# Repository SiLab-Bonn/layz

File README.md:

# layz

Layout tools for SiLab's FR4 PCBs, in-house RDL chips (maskless lithography) and the flex PCBs
that connect them, as one command line tool:

```
layz drc       design rule check of a GDS (gdscheck, with the kit's deck)
layz pcb       GDS -> KiCad .kicad_pcb (copper zones, footprints, vias, outline, stackup)
layz nets      assign zone/via nets from a seed footprint's pad nets
layz hyp       .kicad_pcb or GDS -> HyperLynx .hyp (for SI/PI)
layz svg       GDS -> SVG preview
layz pex       3-D capacitance matrix with FasterCap/FastCap2 (.kicad_pcb, or GDS + stack)
layz field     electric field and potential from a `layz pex --charges` run
layz view      open a result: DRC report in KLayout, or ParaView renders of a field run
layz doctor    which external tools this machine has
```

`layz <command> -h` shows each command's options.

## Install

layz is a standard Python package (`pyproject.toml`, Python 3.12 to 3.15), installed with
Python's own `venv` and `pip`. It also uses tools that are not on PyPI:

| Tool | Needed for | Linux | macOS |
| --- | --- | --- | --- |
| KiCad (its `pcbnew` Python module, `kicad-cli`) | `pcb`, `hyp`, `pex` on boards, schematic netlists | [kicad.org/download/linux](https://www.kicad.org/download/linux/) | [kicad.org/download/macos](https://www.kicad.org/download/macos/) |
| KLayout | viewing GDS and DRC results | [klayout.de/build.html](https://www.klayout.de/build.html) | [klayout.de/build.html](https://www.klayout.de/build.html) |
| FasterCap (default) / FastCap2 | `pex`, `field` | `scripts/build_solvers.sh` (sources: [FasterCap](https://github.com/iic-jku/FasterCap), [FastCap2](https://github.com/martinjankoehler/FastCap2)) | [FasterCap releases](https://github.com/iic-jku/FasterCap/releases) (or `scripts/build_solvers.sh`) |
| gdscheck | `drc` | [github.com/aesc-silicon/gdscheck](https://github.com/aesc-silicon/gdscheck), with Rust's `cargo` ([rust-lang.org/tools/install](https://www.rust-lang.org/tools/install)) | same |
| ParaView (optional) | `view` of field results | [paraview.org/download](https://www.paraview.org/download/) | [paraview.org/download](https://www.paraview.org/download/) |

gdscheck installs with `cargo install --git https://github.com/aesc-silicon/gdscheck gdscheck`.

KLayout's Python module, KLayout-PEX, Shapely and the rest come from PyPI. From the repo root:

```sh
./install.sh                # once; again after a pull that changes dependencies
layz doctor                 # checks klayout, kicad-cli, FasterCap and gdscheck, and more
```

`install.sh` (bash; works from zsh too, on Linux and macOS) makes `.venv/` with the Python that
KiCad's `pcbnew` module is built for (Linux: `python3`, 3.14 on Ubuntu 26.04; macOS: KiCad's own),
checks it's Python 3.12 to 3.15, installs layz into it with `pip install --editable .` (changes in
this repo take effect directly), links `layz` into `~/.local/bin`, and adds that folder to `PATH`
in `~/.bashrc` or `~/.zshrc` if it isn't there yet. `./install.sh --test` also installs pytest,
`./install.sh --uninstall` removes the link. Keep the clone: the DRC decks (`drc/`) and stacks
(`stacks/`) are read from it.

By hand, the same is:

```sh
python3 -m venv --system-site-packages .venv      # system packages: pcbnew comes with KiCad
.venv/bin/pip install --editable .
ln -sf "$PWD/.venv/bin/layz" ~/.local/bin/layz
```

layz finds KiCad's `pcbnew` by itself, also from a venv without the system's packages; set
`LAYZ_KICAD_PYTHONPATH` to the folder holding `pcbnew.py` if it's somewhere unusual.
`layz doctor` exits with an error when a required tool is missing, and warns about optional
ones (HyperLynx via `LAYZ_HYPERLYNX`, FastCap2, ParaView).

On Ubuntu also `sudo apt install cmake g++ libomp-dev libopenblas-dev`, then
`scripts/build_solvers.sh`: it builds FasterCap (iic-jku fork, headless), FastCap2 and a
wxWidgets base library into `~/.local/share/layz` and links the solvers into `~/.local/bin`.
layz finds them on `PATH`, or through `LAYZ_FASTERCAP` / `LAYZ_FASTCAP2`. On macOS see the notes
at the top of the script.

Tests run in the same venv:

```sh
./install.sh --test
.venv/bin/python -m pytest
```

## Stack files

A GDS carries only 2-D shapes; heights, thicknesses and permittivities come from a **stack
file**, one per process, in `stacks/`. It lists the layers top to bottom; z positions are derived
from the order. Every tool reads the same file:

```toml
name = "SiLab RDL, 4 copper"
outline = "70/0"              # GDS layer of the board/die outline

[[layer]]
name = "F.Mask"
type = "mask"                 # mask | copper | dielectric
thickness_um = 1.0
er = 3.3

[[layer]]
name = "F.Cu"                 # KiCad names: F.Cu, In1.Cu, ..., B.Cu
type = "copper"
thickness_um = 0.5
gds = "8/0"
pads = true                   # GDS sub-cells with these shapes become footprint pads
zones = false                 # top-level shapes become copper zones (default true)

[[layer]]
name = "DE_F.Cu"
type = "dielectric"
thickness_um = 4.0
er = 4.5
material = "FR4"
# ... more layers ...

[[via]]
gds = "7/0"
top = "F.Cu"
bottom = "In1.Cu"
```

`layz pcb --stack` writes the stack into the board as its KiCad physical stackup, so the
`.kicad_pcb`, the `.hyp` and the FasterCap model all carry it. A board made in KiCad uses its
own stackup (Board Setup > Physical Stackup). The full format is documented in
[src/layz/stack.py](src/layz/stack.py).

| Stack file | Process | Source |
| --- | --- | --- |
| `uni_bonn_rdl.toml` | Uni Bonn RDL, Al on polyimide (obelix1: M2 + M3 on the chip pads) | asiclab `tech/uni-bonn-rdl` thicknesses, obelix1 KiCad mapping; polyimide εr and 8/0 to confirm |
| `multicb_4L-01.toml` | Multi-CB 4-layer FR4, 1.6 mm | Multi-CB defined buildup 4L-01 (mask assumed: 10 µm, εr 3.3) |
| `multicb_4L-02.toml` | Multi-CB 4-layer FR4, 1.0 mm | Multi-CB defined buildup 4L-02 (mask assumed) |
| `multicb_flex_2F-l.toml` | Multi-CB 2-layer flex, adhesiveless, 161 µm | Multi-CB standard 2F-l |
| `multicb_flex_2F-a.toml` | Multi-CB 2-layer flex, adhesive-bonded, 187 µm | Multi-CB standard 2F-a |

The Multi-CB files are their published standard buildups; for a board ordered with a custom
buildup, copy the closest one and enter the ordered thicknesses and materials.

## GDS -> KiCad -> HyperLynx

```sh
layz hyp example_files/obelix1_ivtx_ladder_v2.gds --stack stacks/uni_bonn_rdl.toml   # one step
```

or step by step, to edit the board in between:

```sh
layz pcb --lay design.gds --stack stacks/uni_bonn_rdl.toml          # -> design.kicad_pcb
# KiCad: Update PCB from Schematic (references and the seed footprint's pad nets)
layz nets design.kicad_pcb --seed-footprint VTX2       # -> design_nets_assigned.kicad_pcb
layz hyp design_nets_assigned.kicad_pcb               # -> design_nets_assigned.hyp
```

`layz pcb`: GDS cells with pad-layer shapes become footprints (one per cell and orientation),
top-level copper becomes filled zones, via layers become blind/buried vias, the outline layer
becomes Edge.Cuts; Y is flipped so the board shows the GDS top view. `nets`: nets propagate from
the seed footprint's pads through touching copper and vias. `hyp`: a re-implementation of KiCad's
HyperLynx exporter (KiCad has it only in the GUI), same records and number format: board
outline, stackup, devices, padstacks, and per net its pins, vias, tracks and zone fills.

## Design rule check

```sh
layz drc --lay design.gds --kit uni-bonn-rdl                  # -> design.lyrdb
layz view design.lyrdb --lay design.gds                     # KLayout with the violation markers
```

Decks are gdscheck PDKs in its own YAML format, one per kit in `drc/<kit>/`.
`drc/uni-bonn-rdl/` is the in-house RDL (maskless lithography), with the layers of asiclab's
`tech/uni-bonn-rdl`: chip pads 68/0, Al M1 1/0, M2 3/0, M3 6/0, polyimide openings V1 2/0,
V2 4/0, pad openings 7/0, outline 70/0.

| Rule | Value |
| --- | --- |
| M1, M2, M3 width, spacing, notch | ≥ 10 µm |
| M1, M2, M3 area (minimum feature 10 × 10 µm) | ≥ 100 µm² |
| V1, V2, pad opening size / spacing (spacing assumed = metal spacing) | ≥ 10 µm |
| V1 by M2, V2 by M2 and M3, pad openings by M3, every side | ≥ 10 µm (pads ≥ 30 × 30 µm) |
| V1 landing on M1 or a chip pad | contained |
| metal density in any 1 × 1 mm window (step 500 µm), inside the outline 70/0 | ≤ 95 % |

Chip pads (68/0) are the chip's and aren't checked. V2 is the 4/0 opening alone (asiclab's
tech has 4/0 AND 5/0; designs draw V2 on 4/0). `--suite geometry` leaves out density. `--benchmark` times each rule on its own (slowest first):
on the obelix1 ladder the M2 and M3 width checks are 98 % of the run. `--tile` is gdscheck's
merge tile; layz uses 20 mm, about 5x faster than 2 mm on the ladder's long planes. The
obelix1 ladder GDS takes about 35 s (18 threads) and reports 261 violations: V2 enclosure
by M2 (52) and M3 (138), density in 19 + 20 windows on M2/M3, 19 notches, 1 width, and 12 at V1
and pad openings.

## Capacitance and fields

```sh
layz pex board.kicad_pcb                              # stack from the board
layz pex chip.gds --stack stacks/uni_bonn_rdl.toml       # stack from the file
layz pex board.kicad_pcb --charges --out run          # also keep charges for fields
layz field run --voltage TOP=1                        # 3-D grid -> run/field.vtk
layz field run --voltage TOP=1 --plane y=5000         # cross-section, PNG + VTK
layz view section run/section_y5000_edge.vtk          # ParaView: heatmap + field lines
layz view geometry run                                # ParaView: the 3-D model
```

A conductor is any copper that touches or is joined by vias (no LVS, no netlist), named by net
(KiCad), by GDS texts or `--name NAME=LAYER@X,Y`. The 3-D model (extrusion, dielectric interfaces,
triangulation into FasterCap's `.lst`/`.geo`) comes from KLayout-PEX's `FasterCapModelBuilder`.
Results: `maxwell_matrix_fF.csv` (Maxwell sign convention: diagonal total, off-diagonal
−mutual) and `spice_caps_fF.csv`.

**Keep `--tolerance` at 1 % or tighter** (the default). With dielectrics FasterCap's first passes
can be far off: plates with εr = 4 gave 2336 fF at 5 % and 3591 fF at 1 %, without an error.
layz warns when FasterCap stops after a single pass.

`--voltage` sets conductor voltages when computing fields; any bias is a superposition of the
solved columns, so it needs no new solve. On Ubuntu ParaView needs `HWLOC_COMPONENTS=-gl`
(`layz view` sets it).

## Checks

`.venv/bin/python -m pytest` (about 3 s):

- GDS -> `.hyp` of the obelix1 RDL design gives the same STACKUP section as the `.hyp` KiCad's GUI
  exported (`example_files/obelix1_ivtx_ladder_with_nets_v3.1.hyp`).
- `tests/plates.gds`, two 1 mm² plates 10 µm apart in vacuum: 918.8 fF (ideal 885 fF + fringe).
- `tests/pcb_plates.kicad_pcb` (two 10 × 10 mm, 35 µm plates on 0.2 mm FR4, from
  `tests/make_pcb_plates.py`) builds the validated 3-D model. Solved at 1 %: 21.54 pF against
  ~21.7 pF from Palmer's edge-corrected formula, 5.16 kV/m in the FR4 at 1 V (ideal 5.0).
- Stack files: heights, validation, KiCad stackup round trip.

## Files

- `src/layz/` the package; `stacks/` process stacks; `example_files/` reference designs
  (GDS, KiCad schematic, a KiCad-exported `.hyp`); `tests/`; `scripts/build_solvers.sh`.

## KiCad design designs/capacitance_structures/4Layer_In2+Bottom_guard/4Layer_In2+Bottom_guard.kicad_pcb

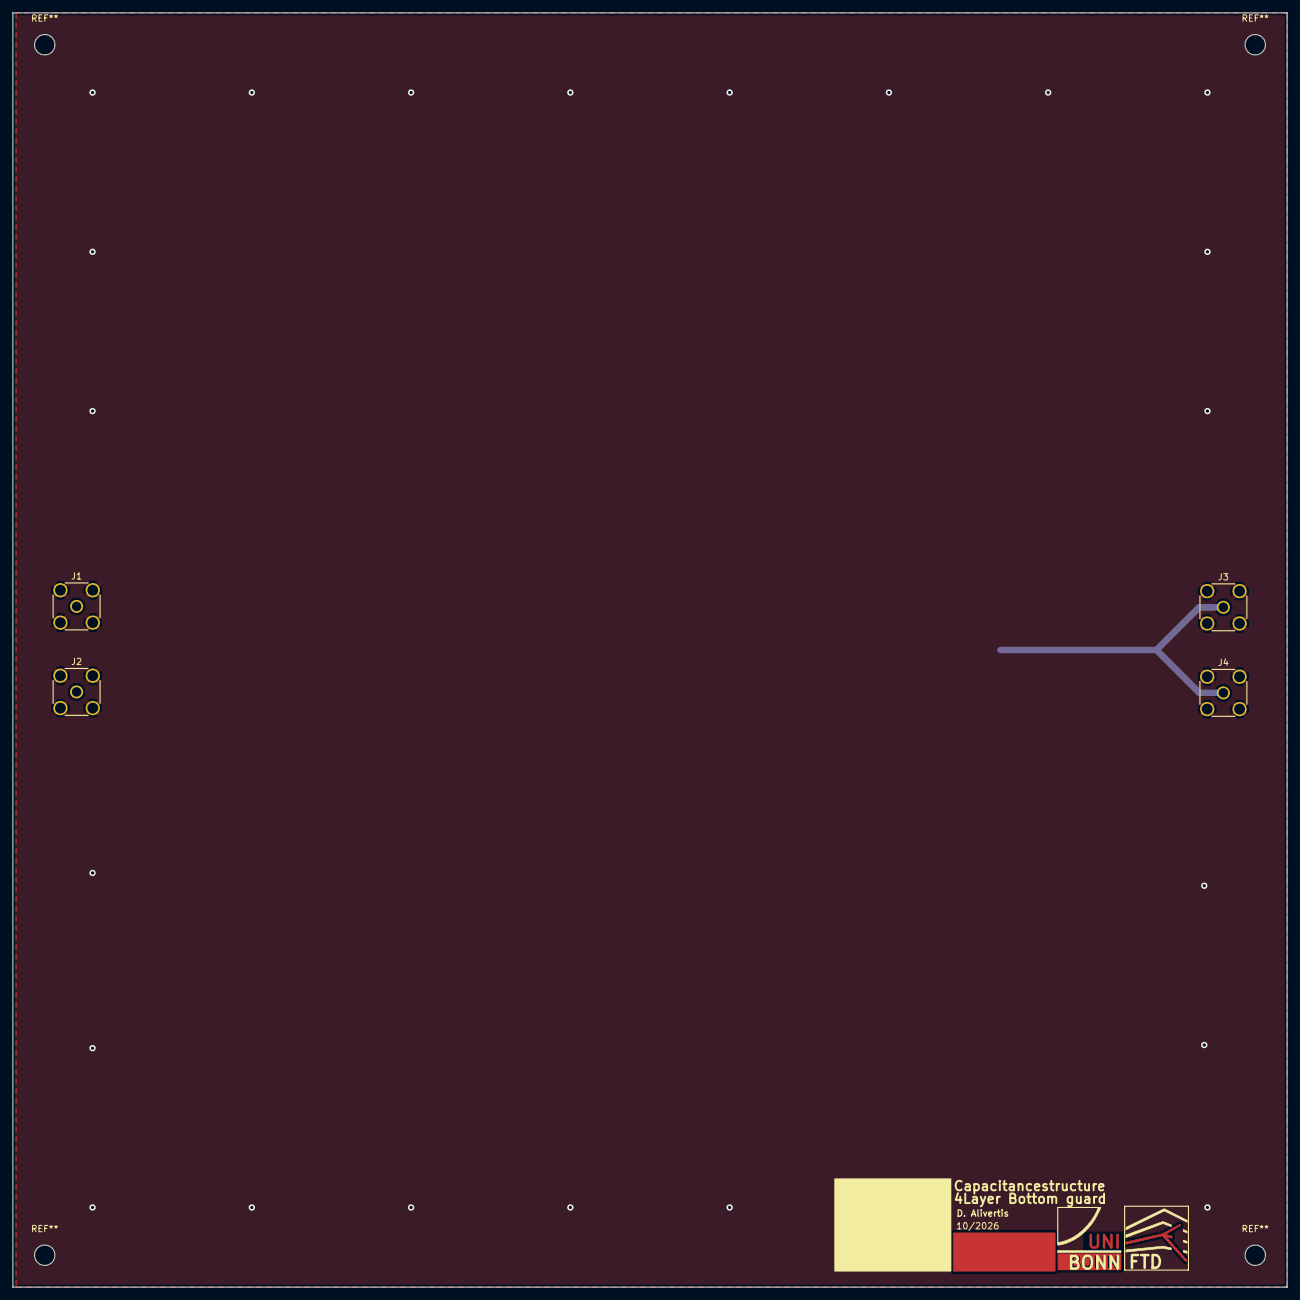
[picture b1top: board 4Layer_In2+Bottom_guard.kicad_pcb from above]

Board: 4 copper layers, 200.0 x 200.0 mm, 4 parts (0 on the bottom side), 3 nets.

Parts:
J1, J2, J3, J4: Conn_Coaxial_Power; SMA_Amphenol_132134_Vertical

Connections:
/Plane bottom: J3.1 (In), J4.1 (In)
/Plane top: J1.1 (In), J2.1 (In)
GNDREF: J1.2 (Ext), J2.2 (Ext), J3.2 (Ext), J4.2 (Ext)

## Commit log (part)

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2026-06-23 Initial gds2kicad converter
2026-06-23 Polish package metadata and example preview
2026-06-23 Resize README preview image
2026-06-23 Document SVG preview generation
